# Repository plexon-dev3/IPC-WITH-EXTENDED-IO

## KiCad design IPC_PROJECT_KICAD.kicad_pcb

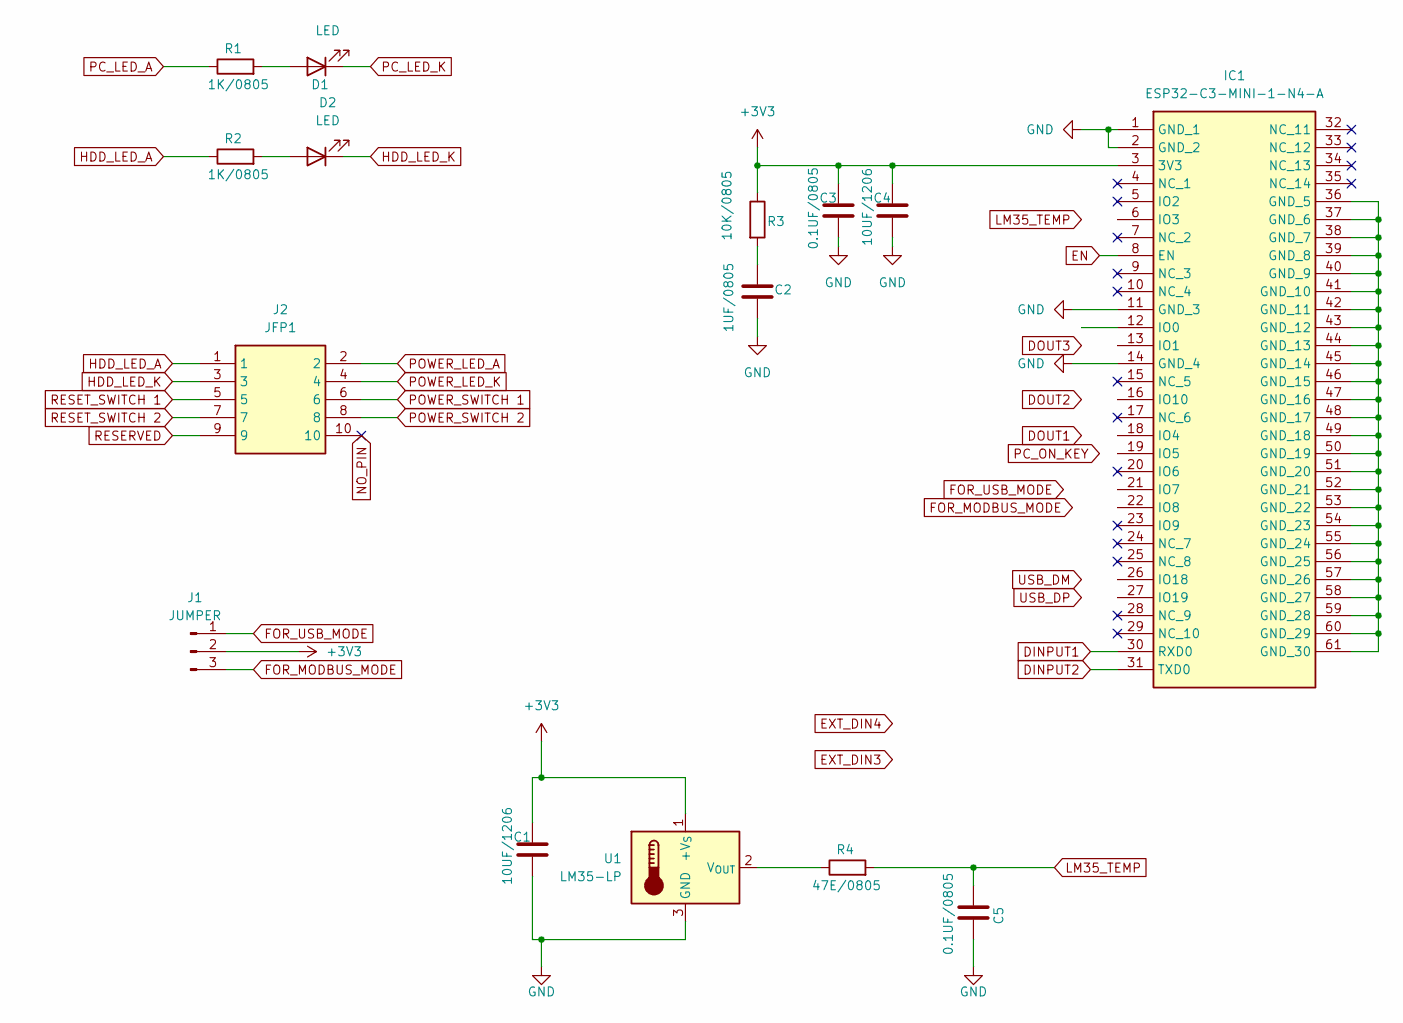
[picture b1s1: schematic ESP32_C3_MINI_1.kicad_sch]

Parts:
C1, C4: 10UF/1206; C_1206_3216Metric
C2: 1UF/0805; C_0805_2012Metric
C3, C5: 0.1UF/0805; C_0805_2012Metric
D1, D2: LED; LED_D3.0mm
IC1: ESP32-C3-MINI-1-N4-A; ESP32C3MINI1N4A; Mouser Part Number N/A
J1: JUMPER; PinHeader_1x03_P2.54mm_Vertical
J2: JFP1; SHDR10W64P254_2X5_2032X889X927P; Mouser Part Number 538-70246-1004
R1, R2: 1K/0805; R_0805_2012Metric
R3: 10K/0805; R_0805_2012Metric
R4: 47E/0805; R_0805_2012Metric
U1: LM35-LP; TO-92_Inline

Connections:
+3V3: C1.1, C3.1, C4.1, IC1.3 (3V3), J1.2, R3.1, U1.1 (+V_{S}); also elsewhere on the board
DINPUT1: IC1.30 (RXD0)
DINPUT2: IC1.31 (TXD0)
EN: IC1.8 (EN)
FOR_MODBUS_MODE: J1.3
FOR_USB_MODE: J1.1
GND: C1.2, C2.2, C3.2, C4.2, C5.2, IC1.1 (GND_1), IC1.2 (GND_2), IC1.11 (GND_3), IC1.14 (GND_4), U1.3 (GND); also elsewhere on the board
HDD_LED_A: J2.1, R2.1
HDD_LED_K: D2.1 (K), J2.3
LM35_TEMP: C5.1, R4.2
NO_PIN: J2.10; also elsewhere on the board
unnamed: C2.1, R3.2
unnamed: D1.2 (A), R1.2
unnamed: D2.2 (A), R2.2
unnamed: IC1.36 (GND_5), IC1.37 (GND_6), IC1.38 (GND_7), IC1.39 (GND_8), IC1.40 (GND_9), IC1.41 (GND_10), IC1.42 (GND_11), IC1.43 (GND_12), IC1.44 (GND_13), IC1.45 (GND_14), IC1.46 (GND_15), IC1.47 (GND_16), IC1.48 (GND_17), IC1.49 (GND_18), IC1.50 (GND_19), IC1.51 (GND_20), IC1.52 (GND_21), IC1.53 (GND_22), IC1.54 (GND_23), IC1.55 (GND_24), IC1.56 (GND_25), IC1.57 (GND_26), IC1.58 (GND_27), IC1.59 (GND_28), IC1.60 (GND_29), IC1.61 (GND_30)
unnamed: R4.1, U1.2 (V_{OUT})
PC_LED_A: R1.1
PC_LED_K: D1.1 (K)
POWER_LED_A: J2.2
POWER_LED_K: J2.4
POWER_SWITCH 1: J2.6
POWER_SWITCH 2: J2.8
RESERVED: J2.9
RESET_SWITCH 1: J2.5
RESET_SWITCH 2: J2.7

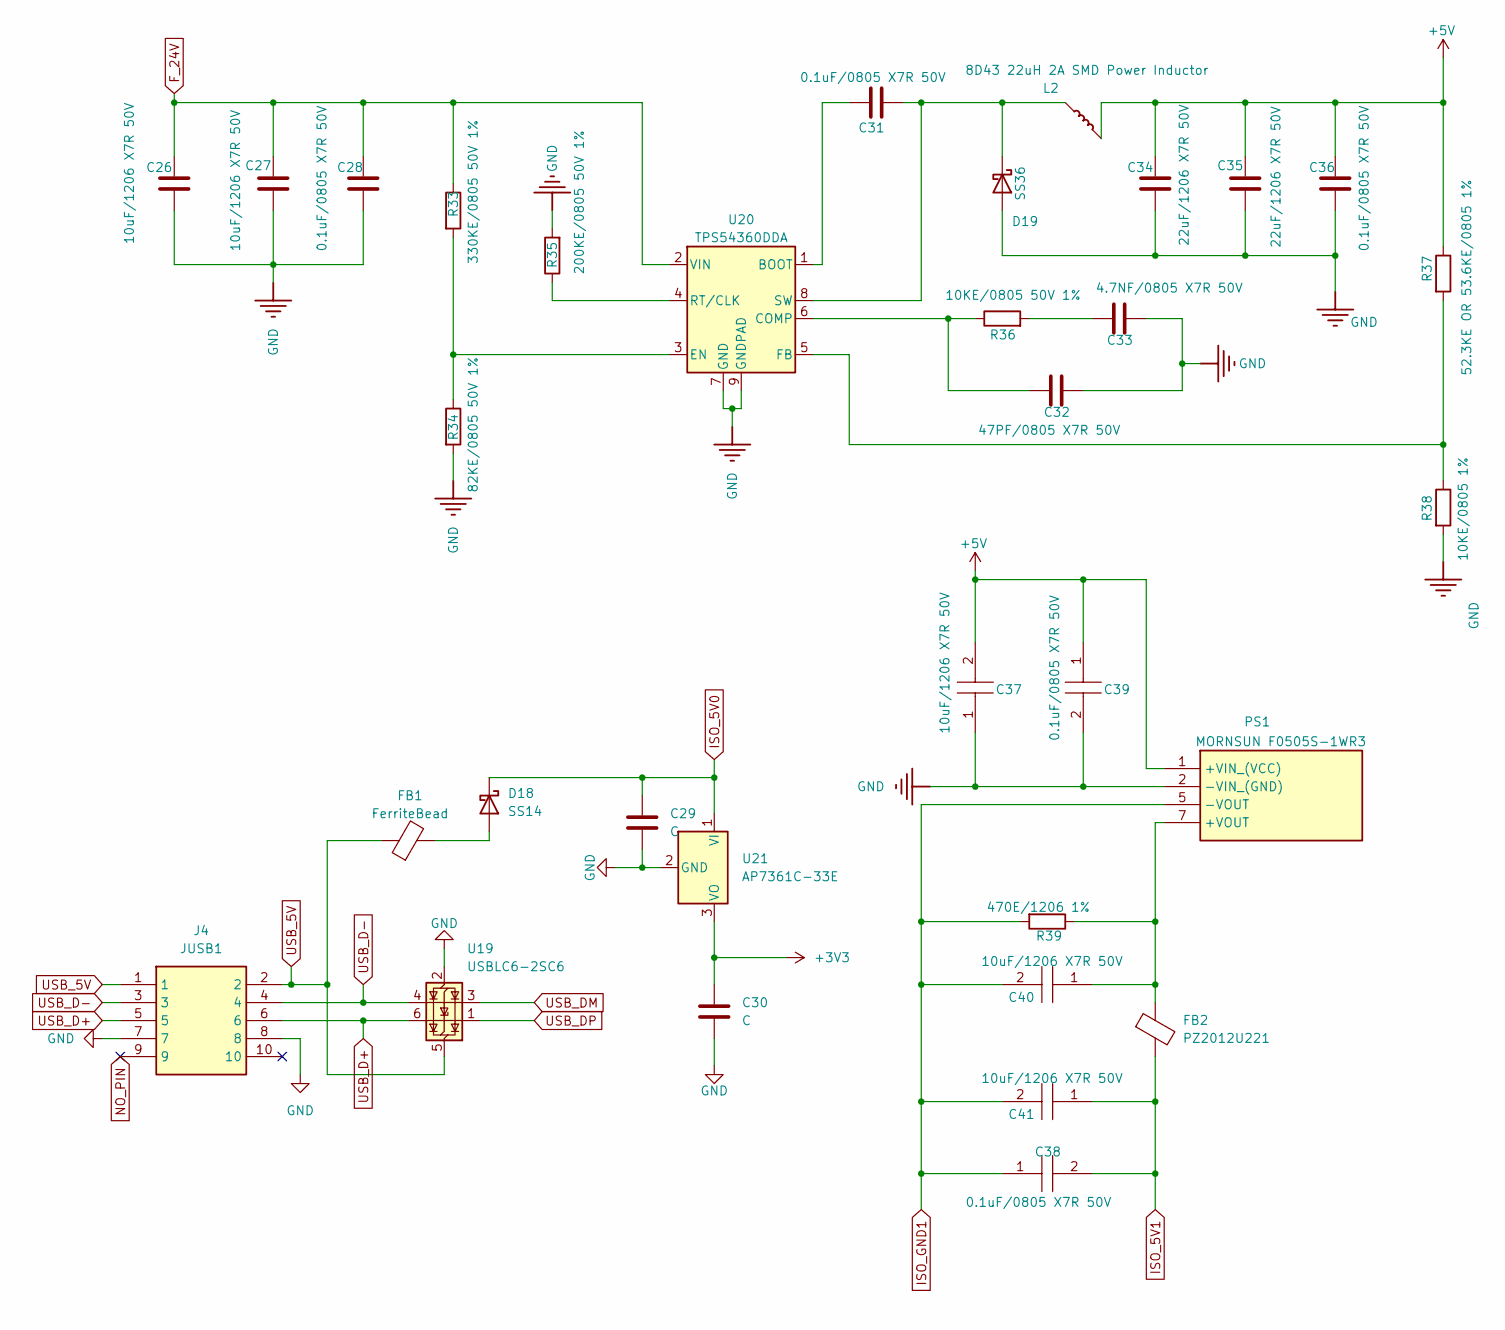
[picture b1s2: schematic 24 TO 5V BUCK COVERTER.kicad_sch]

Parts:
C26, C27: 10uF/1206 X7R 50V; C_1206_3216Metric
C28, C31, C36: 0.1uF/0805 X7R 50V; C_0805_2012Metric
C29, C30: C; C_1206_3216Metric
C32: 47PF/0805 X7R 50V; C_0805_2012Metric
C33: 4.7NF/0805 X7R 50V; C_0805_2012Metric
C34, C35: 22uF/1206 X7R 50V; C_1206_3216Metric
C37, C40, C41: 10uF/1206 X7R 50V; C_1206_3216Metric_Pad1.33x1.80mm_HandSolder; MANUFACTURER_PART_NUMBER C1206C100F1HACTU; MOUSER PART NUMBER 80-C1206C100F1HACTU
C38, C39: 0.1uF/0805 X7R 50V; C_0805_2012Metric_Pad1.18x1.45mm_HandSolder; MANUFACTURER_PART_NUMBER C0805C100F1GACAUTO
D18: SS14; D_SMA
D19: SS36; D_SMA
FB1: FerriteBead; L_0201_0603Metric
FB2: PZ2012U221; L_0805_2012Metric
J4: JUSB1; SHDR10W64P254_2X5_2032X889X927P; Mouser Part Number 538-70246-1004
L2: 8D43 22uH 2A SMD Power Inductor; L_10.4x10.4_H4.8
PS1: MORNSUN F0505S-1WR3; TEA10505HI; Mouser Part Number 495-TEA1-0505HI
R33: 330KE/0805 50V 1%; R_0805_2012Metric
R34: 82KE/0805 50V 1%; R_0805_2012Metric
R35: 200KE/0805 50V 1%; R_0805_2012Metric
R36: 10KE/0805 50V 1%; R_0805_2012Metric
R37: 52.3KE OR 53.6KE/0805 1%; R_0805_2012Metric
R38: 10KE/0805 1%; R_0805_2012Metric
R39: 470E/1206 1%; R_1206_3216Metric
U19: USBLC6-2SC6; SOT-23-6
U20: TPS54360DDA; TI_SO-PowerPAD-8_ThermalVias
U21: AP7361C-33E; SOT-223-3_TabPin2

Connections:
+3V3: C30.1, U21.3 (VO); also elsewhere on the board
+5V: C34.1, C35.1, C36.1, C37.2, C39.1, L2.1, PS1.1 (+VIN_(VCC)), R37.1; also elsewhere on the board
F_24V: C26.1, C27.1, C28.1, R33.1, U20.2 (VIN); also elsewhere on the board
GND: C26.2, C27.2, C28.2, C29.2, C30.2, C32.2, C33.2, C34.2, C35.2, C36.2, C37.1, C39.2, D19.2 (A), J4.7, J4.8, PS1.2 (-VIN_(GND)), R34.2, R35.2, R38.2, U19.2 (GND), U20.7 (GND), U20.9 (GNDPAD), U21.2 (GND); also elsewhere on the board
ISO_5V0: C29.1, D18.1 (K), U21.1 (VI)
ISO_5V1: C38.2, C41.1, FB2.2
ISO_GND1: C38.1, C40.2, C41.2, PS1.5 (-VOUT), R39.2
NO_PIN: J4.9; also elsewhere on the board
unnamed: C33.1, R36.2
unnamed: D18.2 (A), FB1.2
unnamed: C31.2, D19.1 (K), L2.2, U20.8 (SW)
unnamed: C40.1, FB2.1, PS1.7 (+VOUT), R39.1
unnamed: C31.1, U20.1 (BOOT)
unnamed: C32.1, R36.1, U20.6 (COMP)
unnamed: R33.2, R34.1, U20.3 (EN)
unnamed: R37.2, R38.1, U20.5 (FB)
unnamed: R35.1, U20.4 (RT/CLK)
USB_5V: FB1.1, J4.1, J4.2, U19.5 (VBUS)
USB_D+: J4.5, J4.6, U19.6 (I/O1)
USB_D-: J4.3, J4.4, U19.4 (I/O2)
USB_DM: U19.3 (I/O2)
USB_DP: U19.1 (I/O1)

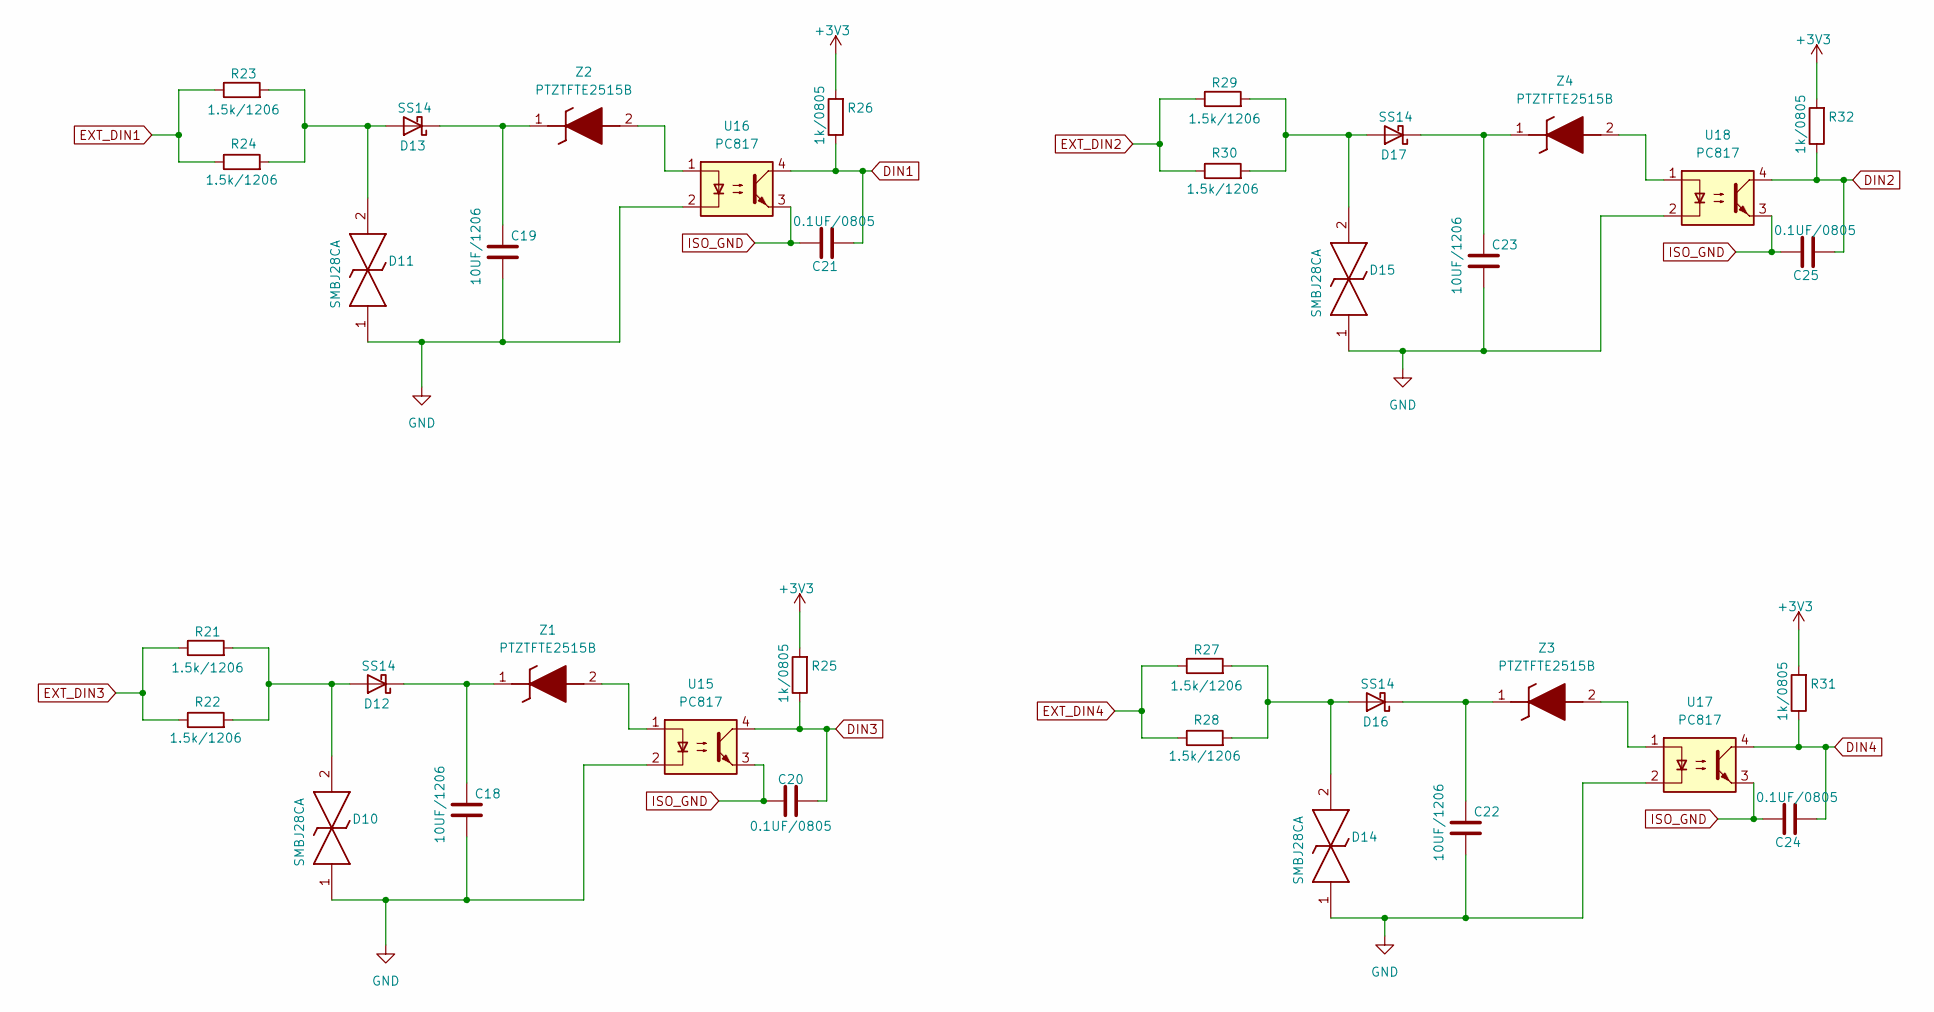
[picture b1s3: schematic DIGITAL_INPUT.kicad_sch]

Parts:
C18, C19, C22, C23: 10UF/1206; C_1206_3216Metric
C20, C21, C24, C25: 0.1UF/0805; C_0805_2012Metric
D10, D11, D14, D15: SMBJ28CA; DIONM5436X261N; Mouser Part Number 576-SMBJ28CA
D12, D13, D16, D17: SS14; D_SMA
R21, R22, R23, R24, R27, R28, R29, R30: 1.5k/1206; R_1206_3216Metric
R25, R26, R31, R32: 1k/0805; R_0805_2012Metric
U15, U16, U17, U18: PC817; DIP-4_W7.62mm
Z1, Z2, Z3, Z4: PTZTFTE2515B; Mouser Part Number 755-PTZTFTE2515B

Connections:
+3V3: R25.2, R26.2, R31.2, R32.2; also elsewhere on the board
DIN1: C21.2, R26.1, U16.4
DIN2: C25.2, R32.1, U18.4
DIN3: C20.2, R25.1, U15.4
DIN4: C24.2, R31.1, U17.4
EXT_DIN1: R23.1, R24.1; also elsewhere on the board
EXT_DIN2: R29.1, R30.1; also elsewhere on the board
EXT_DIN3: R21.1, R22.1; also elsewhere on the board
EXT_DIN4: R27.1, R28.1; also elsewhere on the board
GND: C18.2, C19.2, C22.2, C23.2, D10.1, D11.1, D14.1, D15.1, U15.2, U16.2, U17.2, U18.2; also elsewhere on the board
ISO_GND: C20.1, C21.1, C24.1, C25.1, U15.3, U16.3, U17.3, U18.3; also elsewhere on the board
unnamed: D10.2, D12.2 (A), R21.2, R22.2
unnamed: C18.1, D12.1 (K), Z1.1 (K)
unnamed: D11.2, D13.2 (A), R23.2, R24.2
unnamed: C19.1, D13.1 (K), Z2.1 (K)
unnamed: D14.2, D16.2 (A), R27.2, R28.2
unnamed: C22.1, D16.1 (K), Z3.1 (K)
unnamed: D15.2, D17.2 (A), R29.2, R30.2
unnamed: C23.1, D17.1 (K), Z4.1 (K)
unnamed: U15.1, Z1.2 (A)
unnamed: U16.1, Z2.2 (A)
unnamed: U17.1, Z3.2 (A)
unnamed: U18.1, Z4.2 (A)

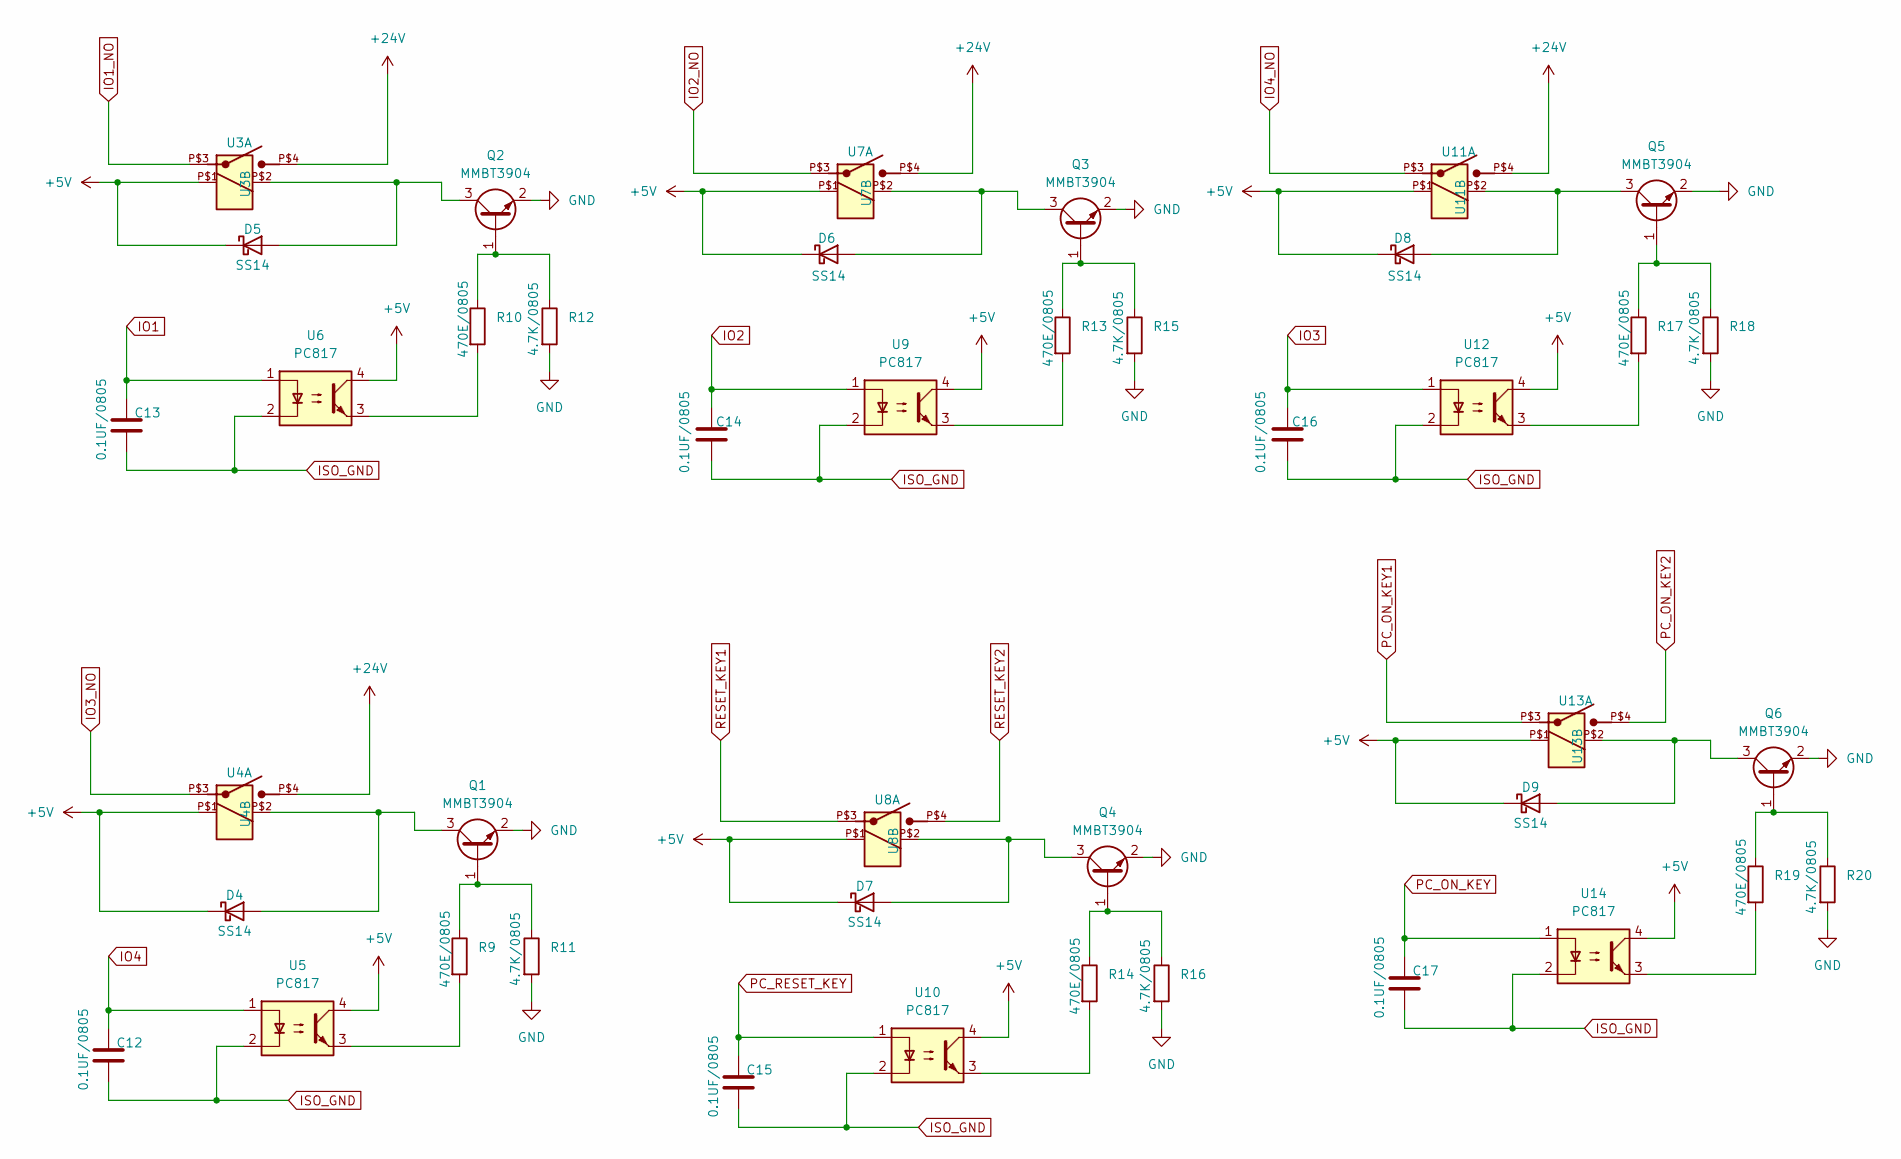
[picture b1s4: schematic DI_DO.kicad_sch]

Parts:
C12, C13, C14, C15, C16, C17: 0.1UF/0805; C_0805_2012Metric
D4, D5, D6, D7, D8, D9: SS14; D_SMA
Q1, Q2, Q3, Q4, Q5, Q6: MMBT3904; SOT-23
R9, R10, R13, R14, R17, R19: 470E/0805; R_0805_2012Metric
R11, R12, R15, R16, R18, R20: 4.7K/0805; R_0805_2012Metric
U3, U4, U7, U8, U11, U13: PCN-105D3MHZ
U5, U6, U9, U10, U12, U14: PC817; DIP-4_W7.62mm

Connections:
+5V: D4.1 (K), D5.1 (K), D6.1 (K), D7.1 (K), D8.1 (K), D9.1 (K), U3.P$1, U4.P$1, U5.4, U6.4, U7.P$1, U8.P$1, U9.4, U10.4, U11.P$1, U12.4, U13.P$1, U14.4; also elsewhere on the board
GND: Q1.2 (E), Q2.2 (E), Q3.2 (E), Q4.2 (E), Q5.2 (E), Q6.2 (E), R11.2, R12.2, R15.2, R16.2, R18.2, R20.2; also elsewhere on the board
IO1: C13.1, U6.1
IO1_NO: U3.P$3; also elsewhere on the board
IO2: C14.1, U9.1
IO2_NO: U7.P$3; also elsewhere on the board
IO3: C16.1, U12.1
IO3_NO: U4.P$3; also elsewhere on the board
IO4: C12.1, U5.1
IO4_NO: U11.P$3; also elsewhere on the board
ISO_GND: C12.2, C13.2, C14.2, C15.2, C16.2, C17.2, U5.2, U6.2, U9.2, U10.2, U12.2, U14.2; also elsewhere on the board
unnamed: D4.2 (A), Q1.3 (C), U4.P$2
unnamed: D5.2 (A), Q2.3 (C), U3.P$2
unnamed: D6.2 (A), Q3.3 (C), U7.P$2
unnamed: D7.2 (A), Q4.3 (C), U8.P$2
unnamed: D8.2 (A), Q5.3 (C), U11.P$2
unnamed: D9.2 (A), Q6.3 (C), U13.P$2
unnamed: Q1.1 (B), R9.1, R11.1
unnamed: Q2.1 (B), R10.1, R12.1
unnamed: Q3.1 (B), R13.1, R15.1
unnamed: Q4.1 (B), R14.1, R16.1
unnamed: Q5.1 (B), R17.1, R18.1
unnamed: Q6.1 (B), R19.1, R20.1
unnamed: R9.2, U5.3
unnamed: R10.2, U6.3
unnamed: R13.2, U9.3
unnamed: R14.2, U10.3
unnamed: R17.2, U12.3
unnamed: R19.2, U14.3
PC_ON_KEY: C17.1, U14.1
PC_ON_KEY1: U13.P$3
PC_ON_KEY2: U13.P$4
PC_RESET_KEY: C15.1, U10.1
RESET_KEY1: U8.P$3
RESET_KEY2: U8.P$4
VIN: U3.P$4, U4.P$4, U7.P$4, U11.P$4; also elsewhere on the board

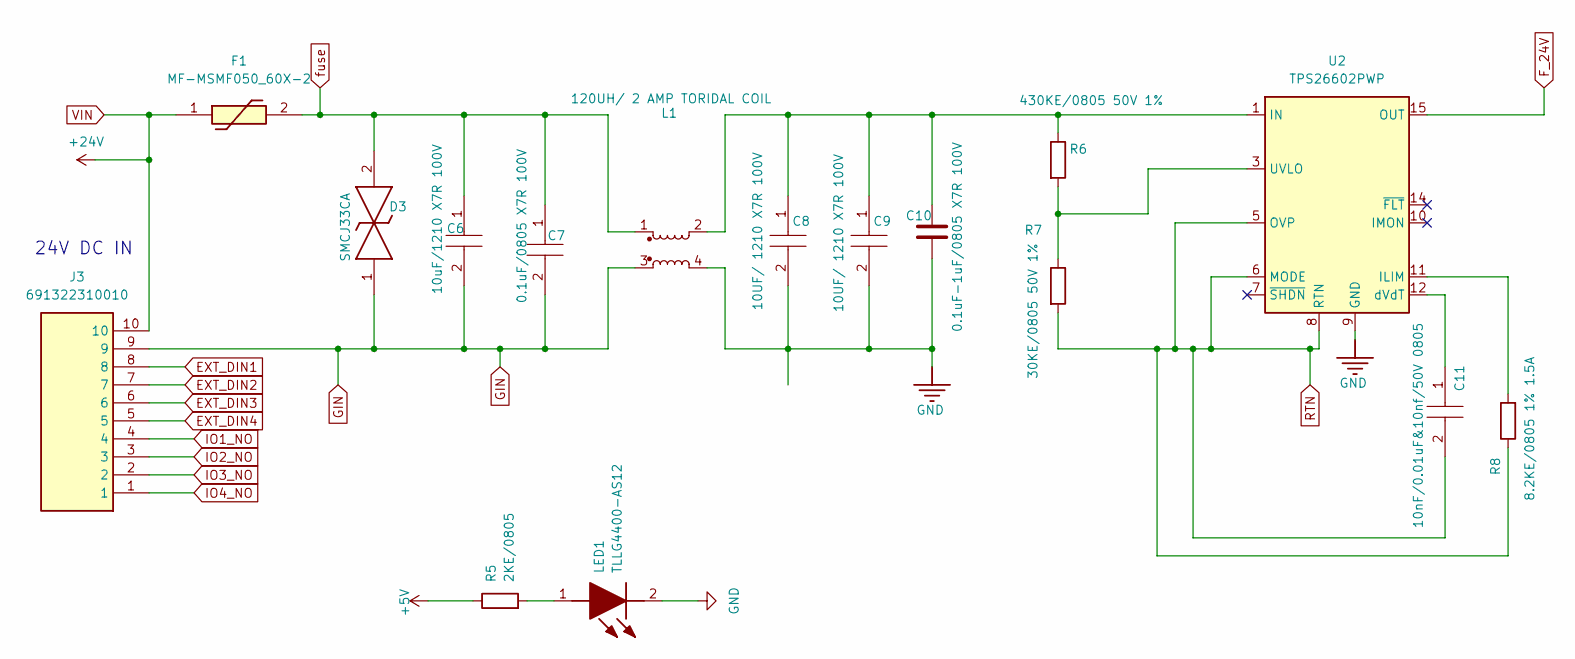
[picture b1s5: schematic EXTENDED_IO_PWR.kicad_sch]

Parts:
C6: 10uF/1210 X7R 100V; C_1210_3225Metric; MANUFACTURER_PART_NUMBER C1206C100F1HACTU; MOUSER PART NUMBER 80-C1206C100F1HACTU
C7: 0.1uF/0805 X7R 100V; C_0805_2012Metric_Pad1.18x1.45mm_HandSolder; MANUFACTURER_PART_NUMBER C0805C100F1GACAUTO
C8, C9: 10UF/ 1210 X7R 100V; C_1210_3225Metric; MANUFACTURER_PART_NUMBER C1206C100F1HACTU; MOUSER PART NUMBER 80-C1206C100F1HACTU
C10: 0.1uF-1uF/0805 X7R 100V; C_0805_2012Metric
C11: 10nF/0.01uF&10nf/50V 0805; C_0805_2012Metric_Pad1.18x1.45mm_HandSolder; MANUFACTURER_PART_NUMBER C0805C100F1GACAUTO
D3: SMCJ33CA; DIONM7959X262N; Mouser Part Number 576-SMCJ33CA
F1: MF-MSMF050_60X-2; MFMSMF05060X2; Manufacturer_Part_Number MF-MSMF050/60X-2
J3: 691322310010; Mouser Part Number 710-691322310010
L1: 120UH/ 2 AMP TORIDAL COIL; Choke_Schaffner_RN102-04-14.0x14.0mm
LED1: TLLG4400-AS12; TLLG4400AS12; Mouser Part Number 78-TLLG4400-AS12
R5: 2KE/0805; R_0805_2012Metric
R6: 430KE/0805 50V 1%; R_0805_2012Metric
R7: 30KE/0805 50V 1%; R_0805_2012Metric
R8: 8.2KE/0805 1% 1.5A; R_0805_2012Metric
U2: TPS26602PWP; HTSSOP-16-1EP_4.4x5mm_P0.65mm_EP3.4x5mm_Mask2.66x2.46mm_The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

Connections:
+5V: R5.1; also elsewhere on the board
EXT_DIN1: J3.8; also elsewhere on the board
EXT_DIN2: J3.7; also elsewhere on the board
EXT_DIN3: J3.6; also elsewhere on the board
EXT_DIN4: J3.5; also elsewhere on the board
F_24V: U2.15 (OUT), U2.16 (OUT); also elsewhere on the board
GIN: C6.2, C7.2, D3.1, J3.9, L1.3
GND: C8.2, C9.2, C10.2, L1.4, LED1.2 (K), U2.9 (GND); also elsewhere on the board
IO1_NO: J3.4; also elsewhere on the board
IO2_NO: J3.3; also elsewhere on the board
IO3_NO: J3.2; also elsewhere on the board
IO4_NO: J3.1; also elsewhere on the board
unnamed: C8.1, C9.1, C10.1, L1.2, R6.1, U2.1 (IN), U2.2 (IN)
unnamed: LED1.1 (A), R5.2
unnamed: R8.2, U2.11 (ILIM)
unnamed: R6.2, R7.1, U2.3 (UVLO)
unnamed: C11.1, U2.12 (dVdT)
RTN: C11.2, R7.2, R8.1, U2.5 (OVP), U2.6 (MODE), U2.8 (RTN), U2.17 (RTN)
VIN: F1.1, J3.10; also elsewhere on the board
fuse: C6.1, C7.1, D3.2, F1.2, L1.1

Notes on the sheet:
24V DC IN

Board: 2 copper layers, 142 parts (1 on the bottom side), 86 nets, no tracks yet.
